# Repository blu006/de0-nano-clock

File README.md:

de0-nano-clock
==============

DE0 FPGA clock (internal clock is used on most versions)

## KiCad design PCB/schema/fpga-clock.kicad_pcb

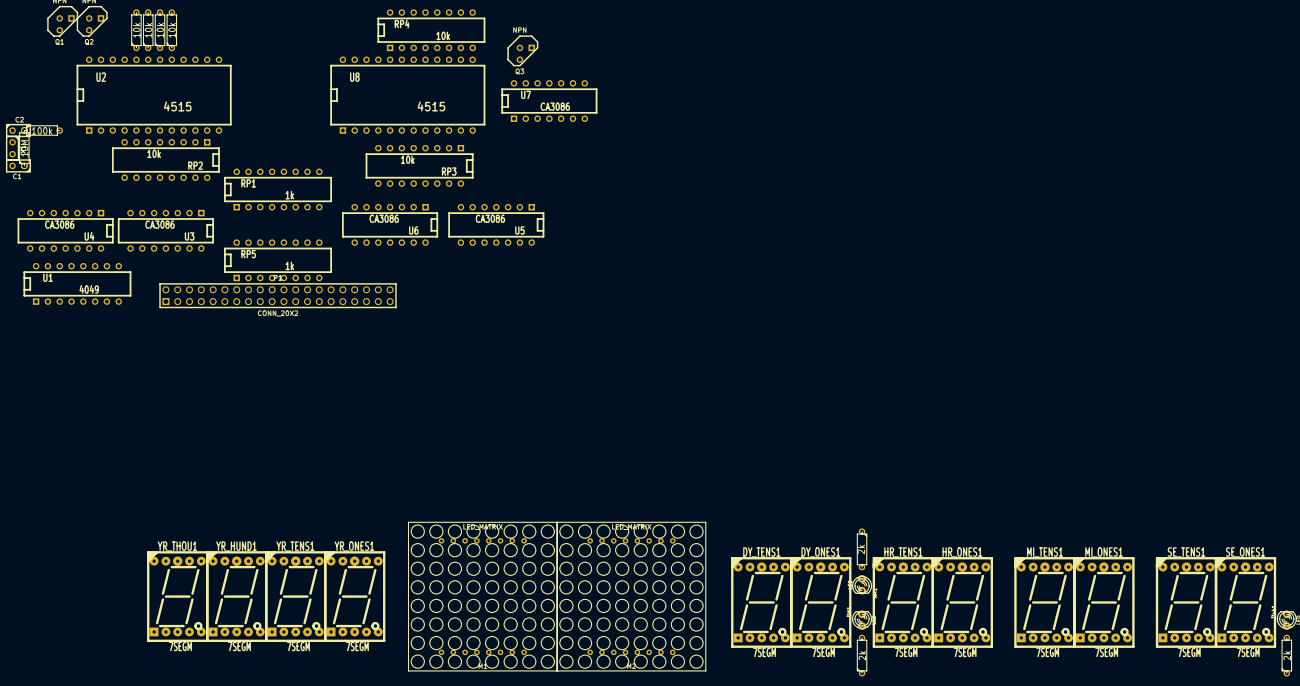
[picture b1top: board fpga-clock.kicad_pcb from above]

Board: 2 copper layers, 46 parts (0 on the bottom side), 134 nets, no tracks yet.

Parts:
AM1: LED; LED-3MM
C1, C2: 12p; C1
DY_ONES1: 7SEGM; HDSP-55xx
DY_TENS1: 7SEGM; HDSP-55xx
HR_ONES1: 7SEGM; HDSP-55xx
HR_TENS1: 7SEGM; HDSP-55xx
M1, M2: LED_MATRIX; led_matrx32x32mm
MI_ONES1: 7SEGM; HDSP-55xx
MI_TENS1: 7SEGM; HDSP-55xx
P1: CONN_20X2; PIN_ARRAY_20X2
PM1: LED; LED-3MM
Q1, Q2, Q3: NPN; TO92
R1: 10M; R3
R2: 100k; R3
R3, R4, R5: 2k; R3
R6, R7, R8, R9: 10k; R3
RP1, RP5: 1k; DIP-16__300
RP2, RP3, RP4: 10k; DIP-16__300
SE_ONES1: 7SEGM; HDSP-55xx
SE_TENS1: 7SEGM; HDSP-55xx
Tick1: LED; LED-3MM
U1: 4049; DIP-16__300
U2, U8: 4515; DIP-24__600
U3, U4, U5, U6, U7: CA3086; DIP-14__300
X1: 32.768kHz; C1
YR_HUND1: 7SEGM; HDSP-55xx
YR_ONES1: 7SEGM; HDSP-55xx
YR_TENS1: 7SEGM; HDSP-55xx
YR_THOU1: 7SEGM; HDSP-55xx

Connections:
3V3: P1.11, U1.1, U2.1, U2.24, U8.1, U8.24
/7seg0: P1.13, RP1.1
/7seg1: P1.15, RP1.2
/7seg2: P1.17, RP1.3
/7seg3: P1.19, RP1.4
/7seg4: P1.21, RP1.5
/7seg5: P1.23, RP1.6
/7seg6: P1.25, RP1.7
/7seg_sel0: P1.31, U2.2
/7seg_sel1: P1.33, U2.3
/7seg_sel2: P1.35, U2.21
/7seg_sel3: P1.37, U2.22
/7segments.sch/7seg_cat0: U3.1, YR_THOU1.8
/7segments.sch/7seg_cat1: U3.5, YR_HUND1.8
/7segments.sch/7seg_cat2: U3.8, YR_TENS1.8
/7segments.sch/7seg_cat3: U3.11, YR_ONES1.8
/7segments.sch/7seg_cat4: DY_TENS1.8, U3.14
/7segments.sch/7seg_cat5: DY_ONES1.8, U4.1
/7segments.sch/7seg_cat6: HR_TENS1.8, U4.5
/7segments.sch/7seg_cat7: HR_ONES1.8, U4.8
/7segments.sch/7seg_cat8: MI_TENS1.8, U4.11
/7segments.sch/7seg_cat9: MI_ONES1.8, U4.14
/7segments.sch/7seg_cat10: Q1.3, SE_TENS1.8
/7segments.sch/7seg_cat11: Q2.3, SE_ONES1.8
/7segments.sch/7seg_n0: RP2.16, U3.2
/7segments.sch/7seg_n1: RP2.15, U3.4
/7segments.sch/7seg_n2: RP2.14, U3.6
/7segments.sch/7seg_n3: RP2.13, U3.9
/7segments.sch/7seg_n4: RP2.12, U3.12
/7segments.sch/7seg_n5: RP2.11, U4.2
/7segments.sch/7seg_n6: RP2.10, U4.4
/7segments.sch/7seg_n7: RP2.9, U4.6
/7segments.sch/7seg_n8: R8.2, U4.9
/7segments.sch/7seg_n9: R6.2, U4.12
/7segments.sch/7seg_n10: Q1.2, R9.2
/7segments.sch/7seg_n11: Q2.2, R7.2
/AM: P1.5, R3.1
/PM: P1.7, R4.1
/Tick: P1.9, R5.1
/col_sel0: P1.32, U8.2
/col_sel1: P1.34, U8.3
/col_sel2: P1.36, U8.21
/col_sel3: P1.38, U8.22
/month_matrix.sch/col0: RP3.16, U5.2
/month_matrix.sch/col1: RP3.15, U5.4
/month_matrix.sch/col2: RP3.14, U5.6
/month_matrix.sch/col3: RP3.13, U5.9
/month_matrix.sch/col4: RP3.12, U5.12
/month_matrix.sch/col5: RP3.11, U6.2
/month_matrix.sch/col6: RP3.10, U6.4
/month_matrix.sch/col7: RP3.9, U6.6
/month_matrix.sch/col8: RP4.16, U6.9
/month_matrix.sch/col9: RP4.15, U6.12
/month_matrix.sch/col10: RP4.14, U7.2
/month_matrix.sch/col11: RP4.13, U7.4
/month_matrix.sch/col12: RP4.12, U7.6
/month_matrix.sch/col13: RP4.11, U7.9
/month_matrix.sch/col14: RP4.10, U7.12
/month_matrix.sch/col15: Q3.2, RP4.9
/month_matrix.sch/col_e0: M1.9, U5.1
/month_matrix.sch/col_e1: M1.14, U5.5
/month_matrix.sch/col_e2: M1.8, U5.8
/month_matrix.sch/col_e3: M1.12, U5.11
/month_matrix.sch/col_e4: M1.1, U5.14
/month_matrix.sch/col_e5: M1.7, U6.1
/month_matrix.sch/col_e6: M1.2, U6.5
/month_matrix.sch/col_e7: M1.5, U6.8
/month_matrix.sch/col_e8: M2.9, U6.11
/month_matrix.sch/col_e9: M2.14, U6.14
/month_matrix.sch/col_e10: M2.8, U7.1
/month_matrix.sch/col_e11: M2.12, U7.5
/month_matrix.sch/col_e12: M2.1, U7.8
/month_matrix.sch/col_e13: M2.7, U7.11
/month_matrix.sch/col_e14: M2.2, U7.14
/month_matrix.sch/col_e15: M2.5, Q3.3
/row0: P1.14, RP5.1
/row1: P1.16, RP5.2
/row2: P1.18, RP5.3
/row3: P1.20, RP5.4
/row4: P1.22, RP5.5
/row5: P1.24, RP5.6
/row6: P1.26, RP5.7
/row7: P1.28, RP5.8
GND: AM1.2, C1.2, C2.1, P1.12, P1.30, PM1.2, Q1.1, Q2.1, Q3.1, Tick1.2, U1.3, U1.5, U1.7, U1.8, U1.9, U2.12, U2.23, U3.3, U3.7, U3.10, U3.13, U4.3, U4.7, U4.10, U4.13, U5.3, U5.7, U5.10, U5.13, U6.3, U6.7, U6.10, U6.13, U7.3, U7.7, U7.10, U7.13, U8.12, U8.23
unnamed: P1.1, U1.15
unnamed: R5.2, Tick1.1
unnamed: AM1.1, R3.2
unnamed: PM1.1, R4.2
unnamed: C1.1, R1.1, U1.11, X1.2
unnamed: R2.2, U1.12, U1.14
unnamed: C2.2, R1.2, R2.1, X1.1
unnamed: RP2.2, U2.9
unnamed: RP2.3, U2.10
unnamed: RP2.4, U2.8
unnamed: RP2.5, U2.7
unnamed: RP2.6, U2.6
unnamed: RP2.7, U2.5
unnamed: RP2.8, U2.4
unnamed: R8.1, U2.18
unnamed: R9.1, U2.20
unnamed: RP2.1, U2.11
unnamed: R6.1, U2.17
unnamed: R7.1, U2.19
unnamed: DY_ONES1.9, DY_TENS1.9, HR_ONES1.9, HR_TENS1.9, MI_ONES1.9, MI_TENS1.9, RP1.11, SE_ONES1.9, SE_TENS1.9, YR_HUND1.9, YR_ONES1.9, YR_TENS1.9, YR_THOU1.9
unnamed: DY_ONES1.10, DY_TENS1.10, HR_ONES1.10, HR_TENS1.10, MI_ONES1.10, MI_TENS1.10, RP1.10, SE_ONES1.10, SE_TENS1.10, YR_HUND1.10, YR_ONES1.10, YR_TENS1.10, YR_THOU1.10
unnamed: DY_ONES1.7, DY_TENS1.7, HR_ONES1.7, HR_TENS1.7, MI_ONES1.7, MI_TENS1.7, RP1.16, SE_ONES1.7, SE_TENS1.7, YR_HUND1.7, YR_ONES1.7, YR_TENS1.7, YR_THOU1.7
unnamed: DY_ONES1.6, DY_TENS1.6, HR_ONES1.6, HR_TENS1.6, MI_ONES1.6, MI_TENS1.6, RP1.15, SE_ONES1.6, SE_TENS1.6, YR_HUND1.6, YR_ONES1.6, YR_TENS1.6, YR_THOU1.6
unnamed: DY_ONES1.4, DY_TENS1.4, HR_ONES1.4, HR_TENS1.4, MI_ONES1.4, MI_TENS1.4, RP1.14, SE_ONES1.4, SE_TENS1.4, YR_HUND1.4, YR_ONES1.4, YR_TENS1.4, YR_THOU1.4
unnamed: DY_ONES1.2, DY_TENS1.2, HR_ONES1.2, HR_TENS1.2, MI_ONES1.2, MI_TENS1.2, RP1.13, SE_ONES1.2, SE_TENS1.2, YR_HUND1.2, YR_ONES1.2, YR_TENS1.2, YR_THOU1.2
unnamed: DY_ONES1.1, DY_TENS1.1, HR_ONES1.1, HR_TENS1.1, MI_ONES1.1, MI_TENS1.1, RP1.12, SE_ONES1.1, SE_TENS1.1, YR_HUND1.1, YR_ONES1.1, YR_TENS1.1, YR_THOU1.1
unnamed: RP3.7, U8.5
unnamed: RP3.1, U8.11
unnamed: RP3.2, U8.9
unnamed: RP3.3, U8.10
unnamed: RP3.4, U8.8
unnamed: RP3.5, U8.7
unnamed: RP3.6, U8.6
unnamed: M1.3, M2.3, RP5.10
unnamed: M1.11, M2.11, RP5.14
unnamed: M1.16, M2.16, RP5.16
unnamed: M1.10, M2.10, RP5.12
unnamed: M1.6, M2.6, RP5.13
unnamed: M1.15, M2.15, RP5.15
unnamed: M1.4, M2.4, RP5.11
unnamed: RP4.4, U8.19
unnamed: RP4.1, U8.18
unnamed: RP4.7, U8.16
unnamed: RP4.8, U8.15
unnamed: RP4.5, U8.14
unnamed: RP4.6, U8.13
unnamed: RP4.3, U8.20
unnamed: RP3.8, U8.4
unnamed: RP4.2, U8.17
unnamed: M1.13, M2.13, RP5.9

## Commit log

2014-01-20 oops, too much swap!
2014-01-20 Initial commit?
2014-01-20 Subtracted some unnecessary files.
2016-11-14 Updated documentation.
